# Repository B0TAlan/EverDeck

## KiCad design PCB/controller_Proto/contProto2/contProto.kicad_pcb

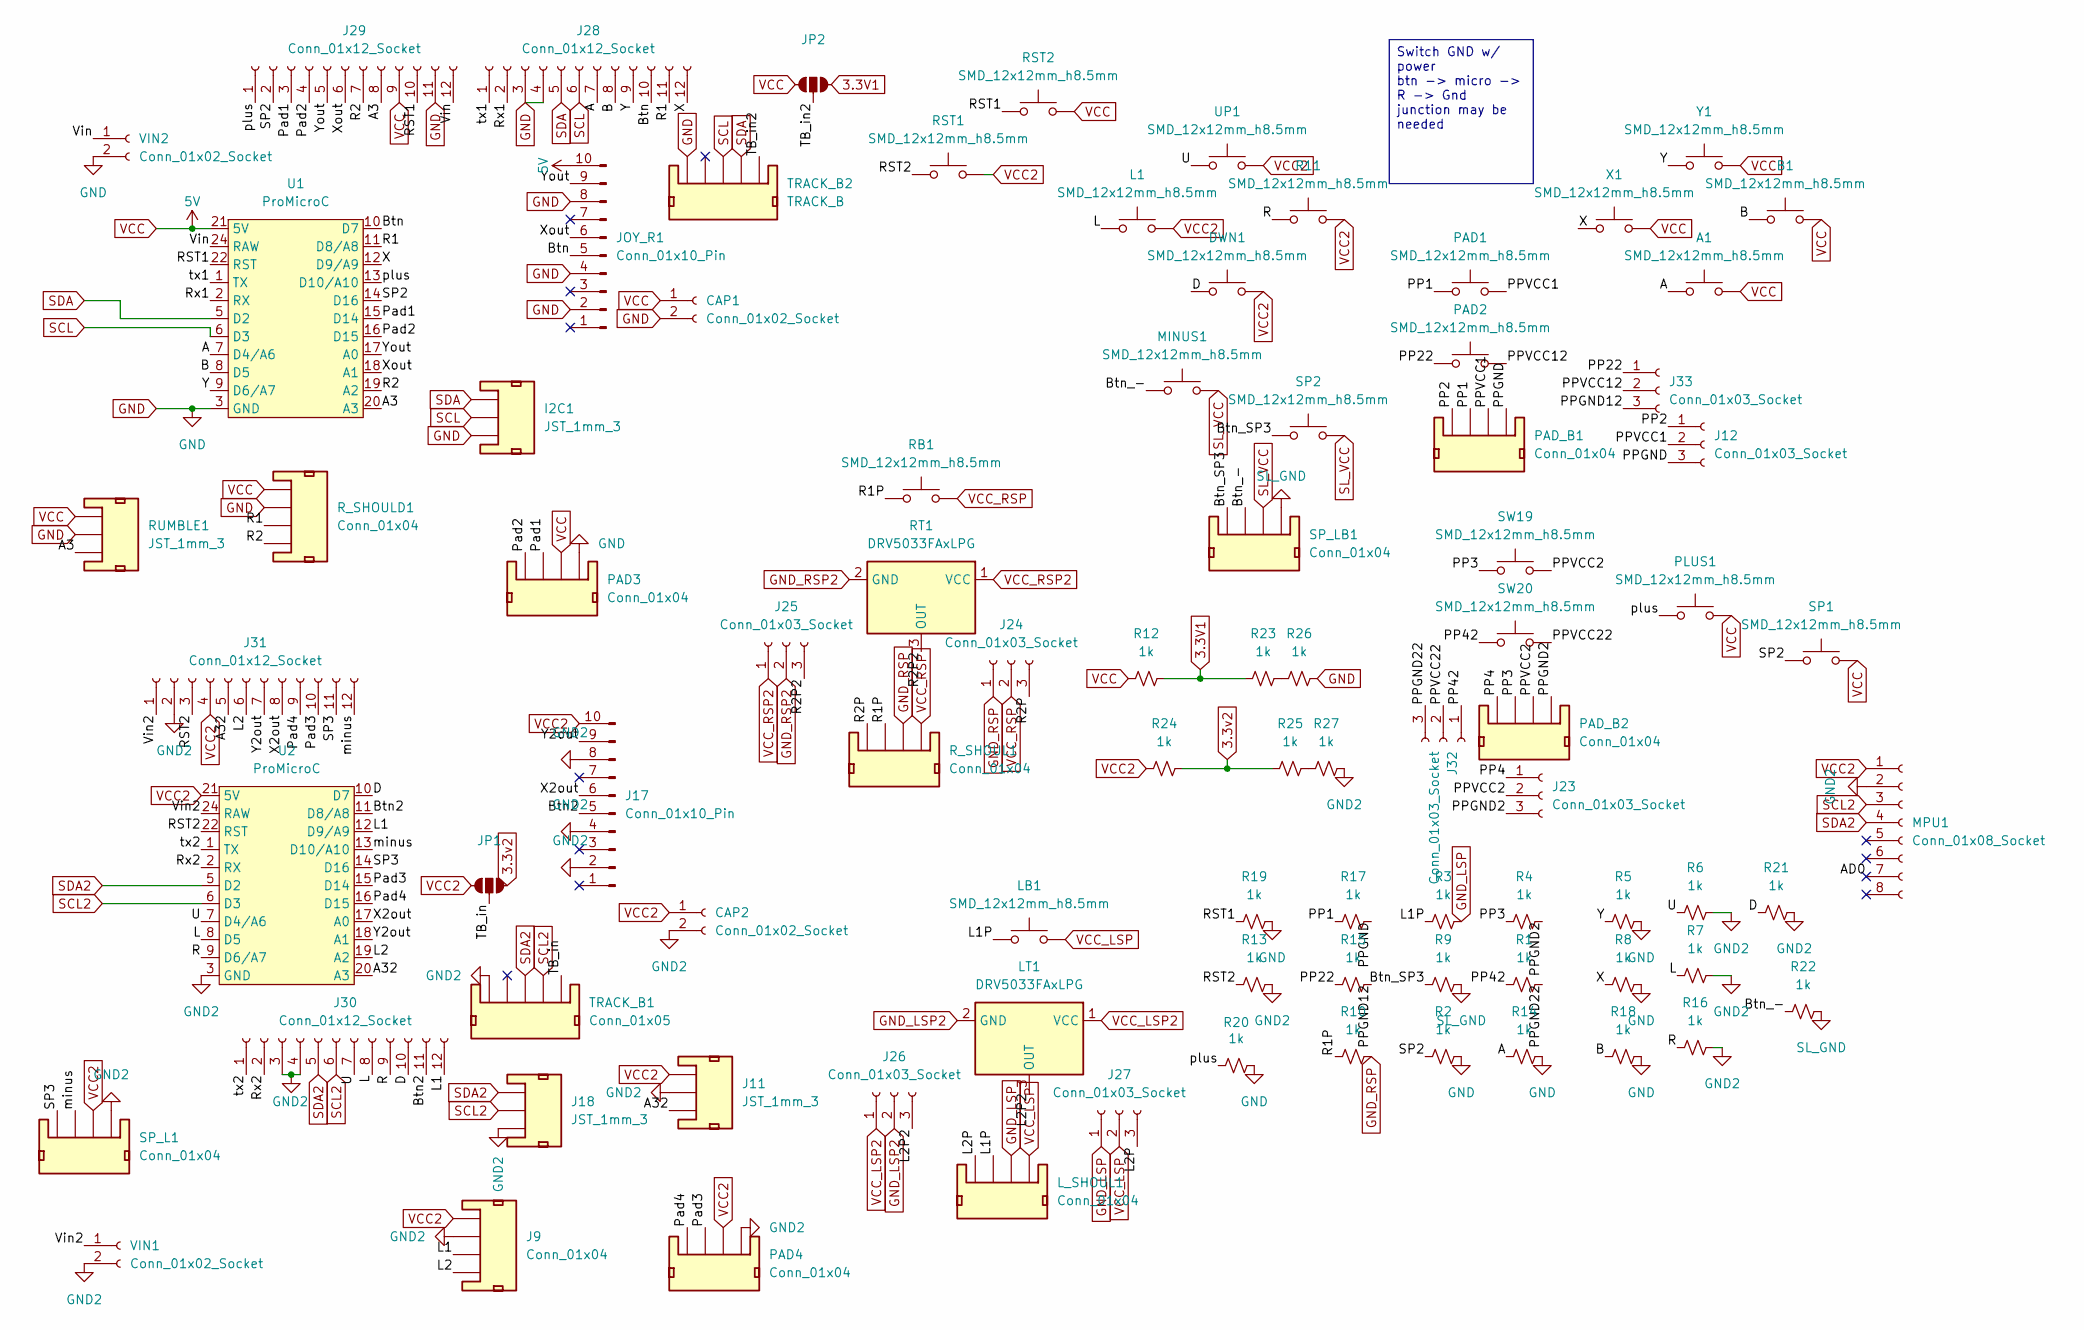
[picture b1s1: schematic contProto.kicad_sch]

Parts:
A1: SMD_12x12mm_h8.5mm; SW_Tactile_SPST_NO_Straight_CK_PTS636Sx25SMTRLFS; Mfg Part# EG4904TR-ND
B1: SMD_12x12mm_h8.5mm; SW_Tactile_SPST_NO_Straight_CK_PTS636Sx25SMTRLFS; Mfg Part# EG4904TR-ND
CAP1, CAP2: Conn_01x02_Socket; PinSocket_1x02_P2.54mm_Vertical
DWN1: SMD_12x12mm_h8.5mm; SW_Tactile_SPST_NO_Straight_CK_PTS636Sx25SMTRLFS; Mfg Part# EG4904TR-ND
I2C1: JST_1mm_3; JST_GH_BM03B-GHS-TBT_1x03-1MP_P1.25mm_Vertical
J9: Conn_01x04; Amphenol_F32Q-1A7x1-11004_1x04-1MP_P0.5mm_Horizontal
J11: JST_1mm_3; PinHeader_1x03_P2.54mm_Vertical
J12, J23, J24, J25, J26, J27, J32, J33: Conn_01x03_Socket; PinSocket_1x03_P2.54mm_Vertical
J17: Conn_01x10_Pin; Amphenol_F32Q-1A7x1-11010_1x10-1MP_P0.5mm_Horizontal
J18: JST_1mm_3; JST_GH_BM03B-GHS-TBT_1x03-1MP_P1.25mm_Vertical
J28, J29, J30, J31: Conn_01x12_Socket; PinSocket_1x12_P2.54mm_Vertical
JOY_R1: Conn_01x10_Pin; Amphenol_F32Q-1A7x1-11010_1x10-1MP_P0.5mm_Horizontal
JP1, JP2: Jumper_3_NO
L1: SMD_12x12mm_h8.5mm; SW_Tactile_SPST_NO_Straight_CK_PTS636Sx25SMTRLFS; Mfg Part# EG4904TR-ND
LB1: SMD_12x12mm_h8.5mm; SW_Tactile_SPST_NO_Straight_CK_PTS636Sx25SMTRLFS; Mfg Part# EG4904TR-ND
LT1: DRV5033FAxLPG; TO-92_Inline
L_SHOUL1: Conn_01x04; Amphenol_F32Q-1A7x1-11004_1x04-1MP_P0.5mm_Horizontal
MINUS1: SMD_12x12mm_h8.5mm; SW_Tactile_SPST_NO_Straight_CK_PTS636Sx25SMTRLFS; Mfg Part# EG4904TR-ND
MPU1: Conn_01x08_Socket; PinSocket_1x08_P2.54mm_Vertical
PAD1, PAD2: SMD_12x12mm_h8.5mm; SW_Tactile_SPST_NO_Straight_CK_PTS636Sx25SMTRLFS; Mfg Part# EG4904TR-ND
PAD3, PAD4: Conn_01x04; Amphenol_F32Q-1A7x1-11004_1x04-1MP_P0.5mm_Horizontal
PAD_B1, PAD_B2: Conn_01x04; Amphenol_F32Q-1A7x1-11004_1x04-1MP_P0.5mm_Horizontal
PLUS1: SMD_12x12mm_h8.5mm; SW_Tactile_SPST_NO_Straight_CK_PTS636Sx25SMTRLFS; Mfg Part# EG4904TR-ND
R1, R2, R3, R4, R5, R6, R7, R8, R9, R10, R12, R13, R14, R15, R16, R17, R18, R19, R20, R21, R22, R23, R24, R25, R26, R27: 1k; R_0805_2012Metric
R11: SMD_12x12mm_h8.5mm; SW_Tactile_SPST_NO_Straight_CK_PTS636Sx25SMTRLFS; Mfg Part# EG4904TR-ND
RB1: SMD_12x12mm_h8.5mm; SW_Tactile_SPST_NO_Straight_CK_PTS636Sx25SMTRLFS; Mfg Part# EG4904TR-ND
RST1, RST2: SMD_12x12mm_h8.5mm; SW_Tactile_SPST_NO_Straight_CK_PTS636Sx25SMTRLFS; Mfg Part# EG4904TR-ND
RT1: DRV5033FAxLPG; TO-92_Inline
RUMBLE1: JST_1mm_3; PinHeader_1x03_P2.54mm_Vertical
R_SHOUL1: Conn_01x04; Amphenol_F32Q-1A7x1-11004_1x04-1MP_P0.5mm_Horizontal
R_SHOULD1: Conn_01x04; Amphenol_F32Q-1A7x1-11004_1x04-1MP_P0.5mm_Horizontal
SP1, SP2: SMD_12x12mm_h8.5mm; SW_Tactile_SPST_NO_Straight_CK_PTS636Sx25SMTRLFS; Mfg Part# EG4904TR-ND
SP_L1: Conn_01x04; Amphenol_F32Q-1A7x1-11004_1x04-1MP_P0.5mm_Horizontal
SP_LB1: Conn_01x04; Amphenol_F32Q-1A7x1-11004_1x04-1MP_P0.5mm_Horizontal
SW19, SW20: SMD_12x12mm_h8.5mm; SW_Tactile_SPST_NO_Straight_CK_PTS636Sx25SMTRLFS; Mfg Part# EG4904TR-ND
TRACK_B1: Conn_01x05; PinHeader_1x05_P2.54mm_Vertical
TRACK_B2: TRACK_B; PinHeader_1x05_P2.54mm_Vertical
U1, U2: ProMicroC
UP1: SMD_12x12mm_h8.5mm; SW_Tactile_SPST_NO_Straight_CK_PTS636Sx25SMTRLFS; Mfg Part# EG4904TR-ND
VIN1, VIN2: Conn_01x02_Socket; PinSocket_1x02_P2.54mm_Vertical
X1: SMD_12x12mm_h8.5mm; SW_Tactile_SPST_NO_Straight_CK_PTS636Sx25SMTRLFS; Mfg Part# EG4904TR-ND
Y1: SMD_12x12mm_h8.5mm; SW_Tactile_SPST_NO_Straight_CK_PTS636Sx25SMTRLFS; Mfg Part# EG4904TR-ND

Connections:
3.3V1: JP2.3 (C), R12.2, R23.1
3.3v2: JP1.3 (C), R24.2, R25.1
/A: A1.1, J28.7, R14.1, U1.7 (D4/A6)
/A3: J29.8, RUMBLE1.3, U1.20 (A3)
/A32: J11.3, J31.5, U2.20 (A3)
/AD0: MPU1.7
/B: B1.1, J28.8, R18.1, U1.8 (D5)
/Btn: J28.10, JOY_R1.5, U1.10 (D7)
/Btn2: J17.5, J30.11, U2.11 (D8/A8)
/Btn_-: MINUS1.1, R22.1, SP_LB1.3
/Btn_SP3: R9.1, SP2.1, SP_LB1.4
/D: DWN1.1, J30.10, R21.1, U2.10 (D7)
/L: J30.8, L1.1, R7.1, U2.8 (D5)
/L1: J9.3, J30.12, U2.12 (D9/A9)
/L1P: LB1.1, L_SHOUL1.3, R3.1
/L2: J9.4, J31.6, U2.19 (A2)
/L2P: J27.3, L_SHOUL1.4
/L2P2: J26.3, LT1.3 (OUT)
/PP1: PAD1.1, PAD_B1.3, R17.1
/PP2: J12.1, PAD_B1.4
/PP3: PAD_B2.3, R4.1, SW19.1
/PP4: J23.1, PAD_B2.4
/PP22: J33.1, PAD2.1, R15.1
/PP42: J32.1, R1.1, SW20.1
/PPGND: J12.3, PAD_B1.1, R17.2
/PPGND2: J23.3, PAD_B2.1, R4.2
/PPGND12: J33.3, R15.2
/PPGND22: J32.3, R1.2
/PPVCC1: J12.2, PAD1.2, PAD_B1.2
/PPVCC2: J23.2, PAD_B2.2, SW19.2
/PPVCC12: J33.2, PAD2.2
/PPVCC22: J32.2, SW20.2
/Pad1: J29.3, PAD3.3, U1.15 (D14)
/Pad2: J29.4, PAD3.4, U1.16 (D15)
/Pad3: J31.10, PAD4.3, U2.15 (D14)
/Pad4: J31.9, PAD4.4, U2.16 (D15)
/R: J30.9, R11.1, R16.1, U2.9 (D6/A7)
/R1: J28.11, R_SHOULD1.3, U1.11 (D8/A8)
/R1P: R10.1, RB1.1, R_SHOUL1.3
/R2: J29.7, R_SHOULD1.4, U1.19 (A2)
/R2P: J24.3, R_SHOUL1.4
/R2P2: J25.3, RT1.3 (OUT)
/RST1: J29.10, R19.1, RST2.1, U1.22 (RST)
/RST2: J31.3, R13.1, RST1.1, U2.22 (RST)
/Rx1: J28.2, U1.2 (RX)
/Rx2: J30.2, U2.2 (RX)
/SP2: J29.2, R2.1, SP1.1, U1.14 (D16)
/SP3: J31.11, SP_L1.4, U2.14 (D16)
/TB_in: JP1.2 (B), TRACK_B1.1
/TB_in2: JP2.2 (B), TRACK_B2.1
/U: J30.7, R6.1, U2.7 (D4/A6), UP1.1
/Vin: J29.12, U1.24 (RAW), VIN2.1
/Vin2: J31.1, U2.24 (RAW), VIN1.1
/X: J28.12, R8.1, U1.12 (D9/A9), X1.1
/X2out: J17.6, J31.8, U2.17 (A0)
/Xout: J29.6, JOY_R1.6, U1.18 (A1)
/Y: J28.9, R5.1, U1.9 (D6/A7), Y1.1
/Y2out: J17.9, J31.7, U2.18 (A1)
/Yout: J29.5, JOY_R1.9, U1.17 (A0)
/minus: J31.12, SP_L1.3, U2.13 (D10/A10)
/plus: J29.1, PLUS1.1, R20.1, U1.13 (D10/A10)
/tx1: J28.1, U1.1 (TX)
/tx2: J30.1, U2.1 (TX)
GND: CAP1.2, I2C1.3, J28.3, J28.4, J29.11, JOY_R1.2, JOY_R1.4, JOY_R1.8, PAD3.1, R2.2, R5.2, R8.2, R14.2, R18.2, R19.2, R20.2, R26.2, RUMBLE1.2, R_SHOULD1.2, TRACK_B2.5, U1.3 (GND), U1.4 (GND), U1.23 (GND), VIN2.2
GND2: CAP2.2, J9.2, J11.2, J17.2, J17.4, J17.8, J18.3, J30.3, J30.4, J31.2, MPU1.2, PAD4.1, R6.2, R7.2, R13.2, R16.2, R21.2, R27.2, SP_L1.1, TRACK_B1.5, U2.3 (GND), U2.4 (GND), U2.23 (GND), VIN1.2
GND_LSP: J27.1, L_SHOUL1.2, R3.2
GND_LSP2: J26.2, LT1.2 (GND)
GND_RSP: J24.1, R10.2, R_SHOUL1.2
GND_RSP2: J25.2, RT1.2 (GND)
unnamed: R23.2, R26.1
unnamed: R25.2, R27.1
SCL: I2C1.2, J28.6, TRACK_B2.3, U1.6 (D3)
SCL2: J18.2, J30.6, MPU1.3, TRACK_B1.2, U2.6 (D3)
SDA: I2C1.1, J28.5, TRACK_B2.2, U1.5 (D2)
SDA2: J18.1, J30.5, MPU1.4, TRACK_B1.3, U2.5 (D2)
SL_GND: R9.2, R22.2, SP_LB1.1
SL_VCC: MINUS1.2, SP2.2, SP_LB1.2
VCC: A1.2, B1.2, CAP1.1, J29.9, JOY_R1.10, JP2.1 (A), PAD3.2, PLUS1.2, R12.1, RST2.2, RUMBLE1.1, R_SHOULD1.1, SP1.2, U1.21 (5V), X1.2, Y1.2
VCC2: CAP2.1, DWN1.2, J9.1, J11.1, J17.10, J31.4, JP1.1 (A), L1.2, MPU1.1, PAD4.2, R11.2, R24.1, RST1.2, SP_L1.2, U2.21 (5V), UP1.2
VCC_LSP: J27.2, LB1.2, L_SHOUL1.1
VCC_LSP2: J26.1, LT1.1 (VCC)
VCC_RSP: J24.2, RB1.2, R_SHOUL1.1
VCC_RSP2: J25.1, RT1.1 (VCC)

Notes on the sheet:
Switch GND w/ power btn -> micro -> R -> Gnd junction may be needed

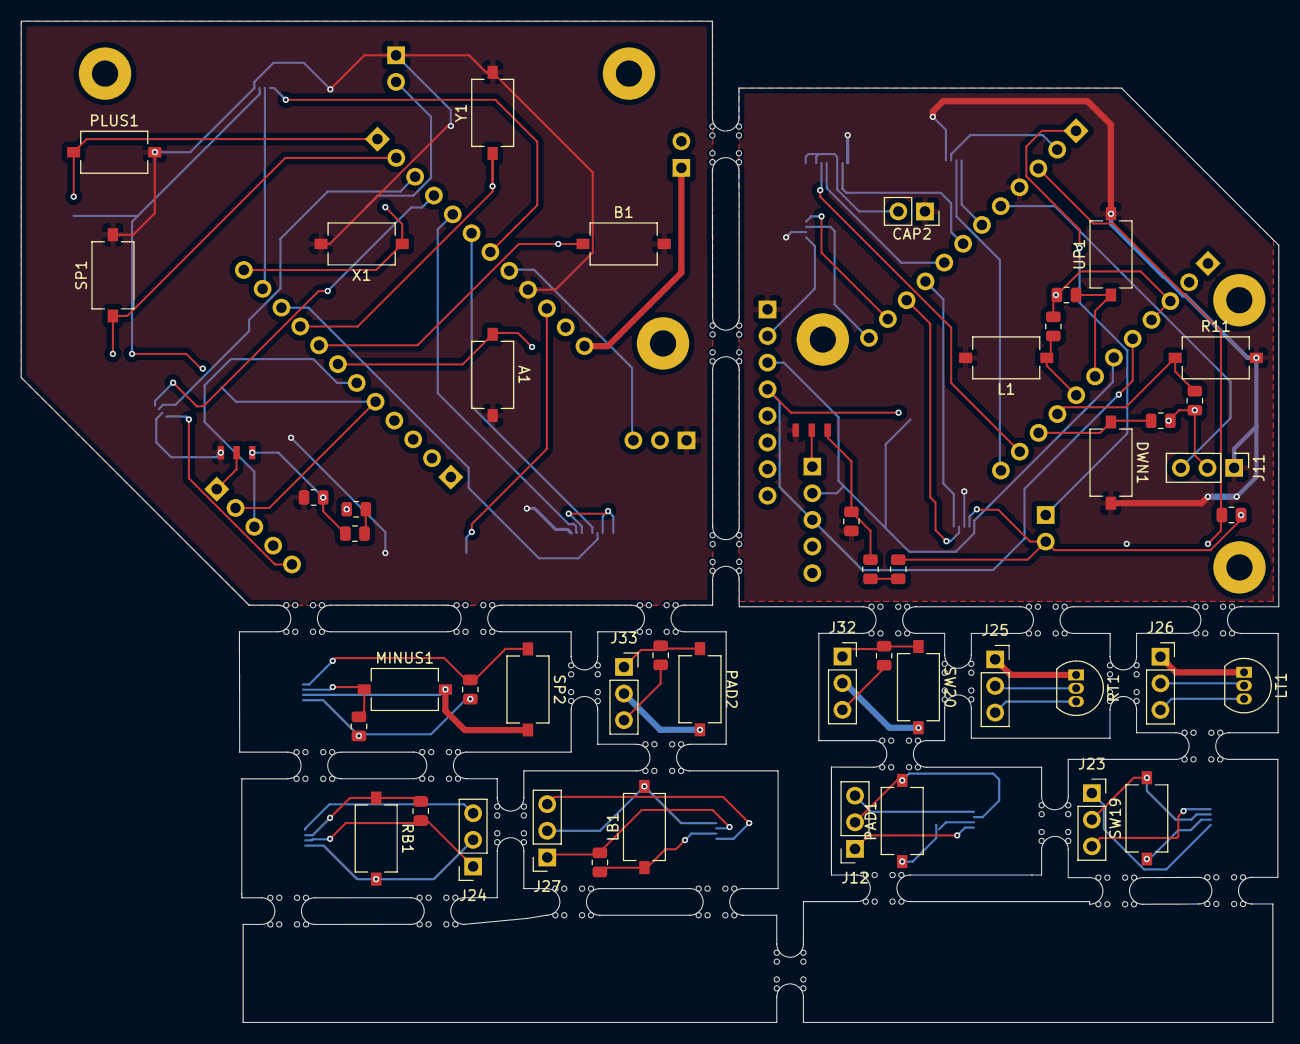
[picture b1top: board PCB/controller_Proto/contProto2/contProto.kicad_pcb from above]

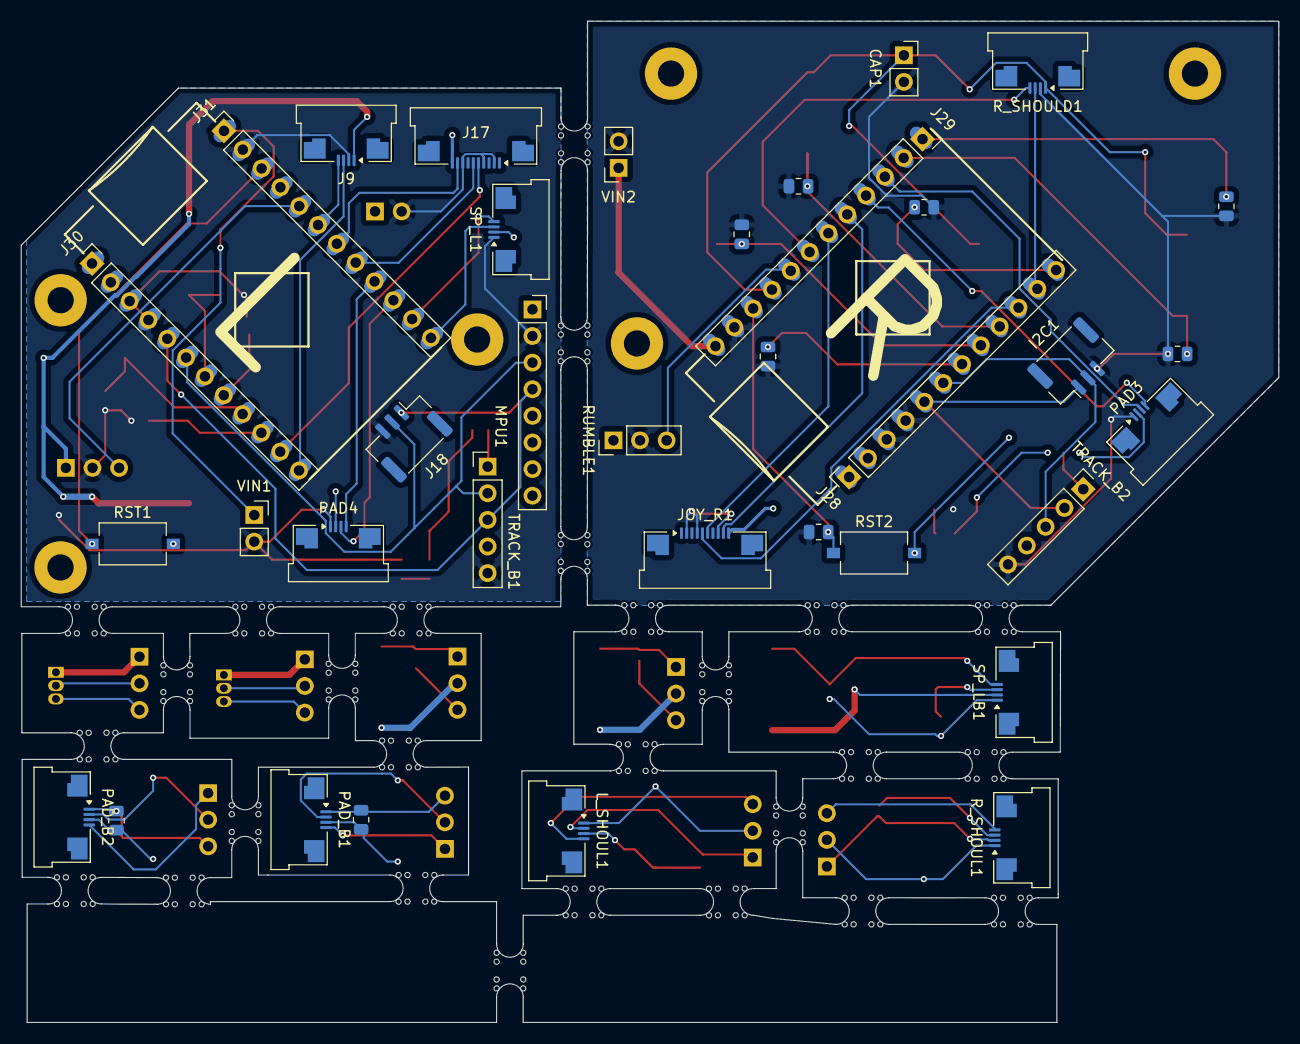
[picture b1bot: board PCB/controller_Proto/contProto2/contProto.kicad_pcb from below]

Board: 2 copper layers, 120.0 x 95.5 mm, 87 parts (38 on the bottom side), 82 nets.

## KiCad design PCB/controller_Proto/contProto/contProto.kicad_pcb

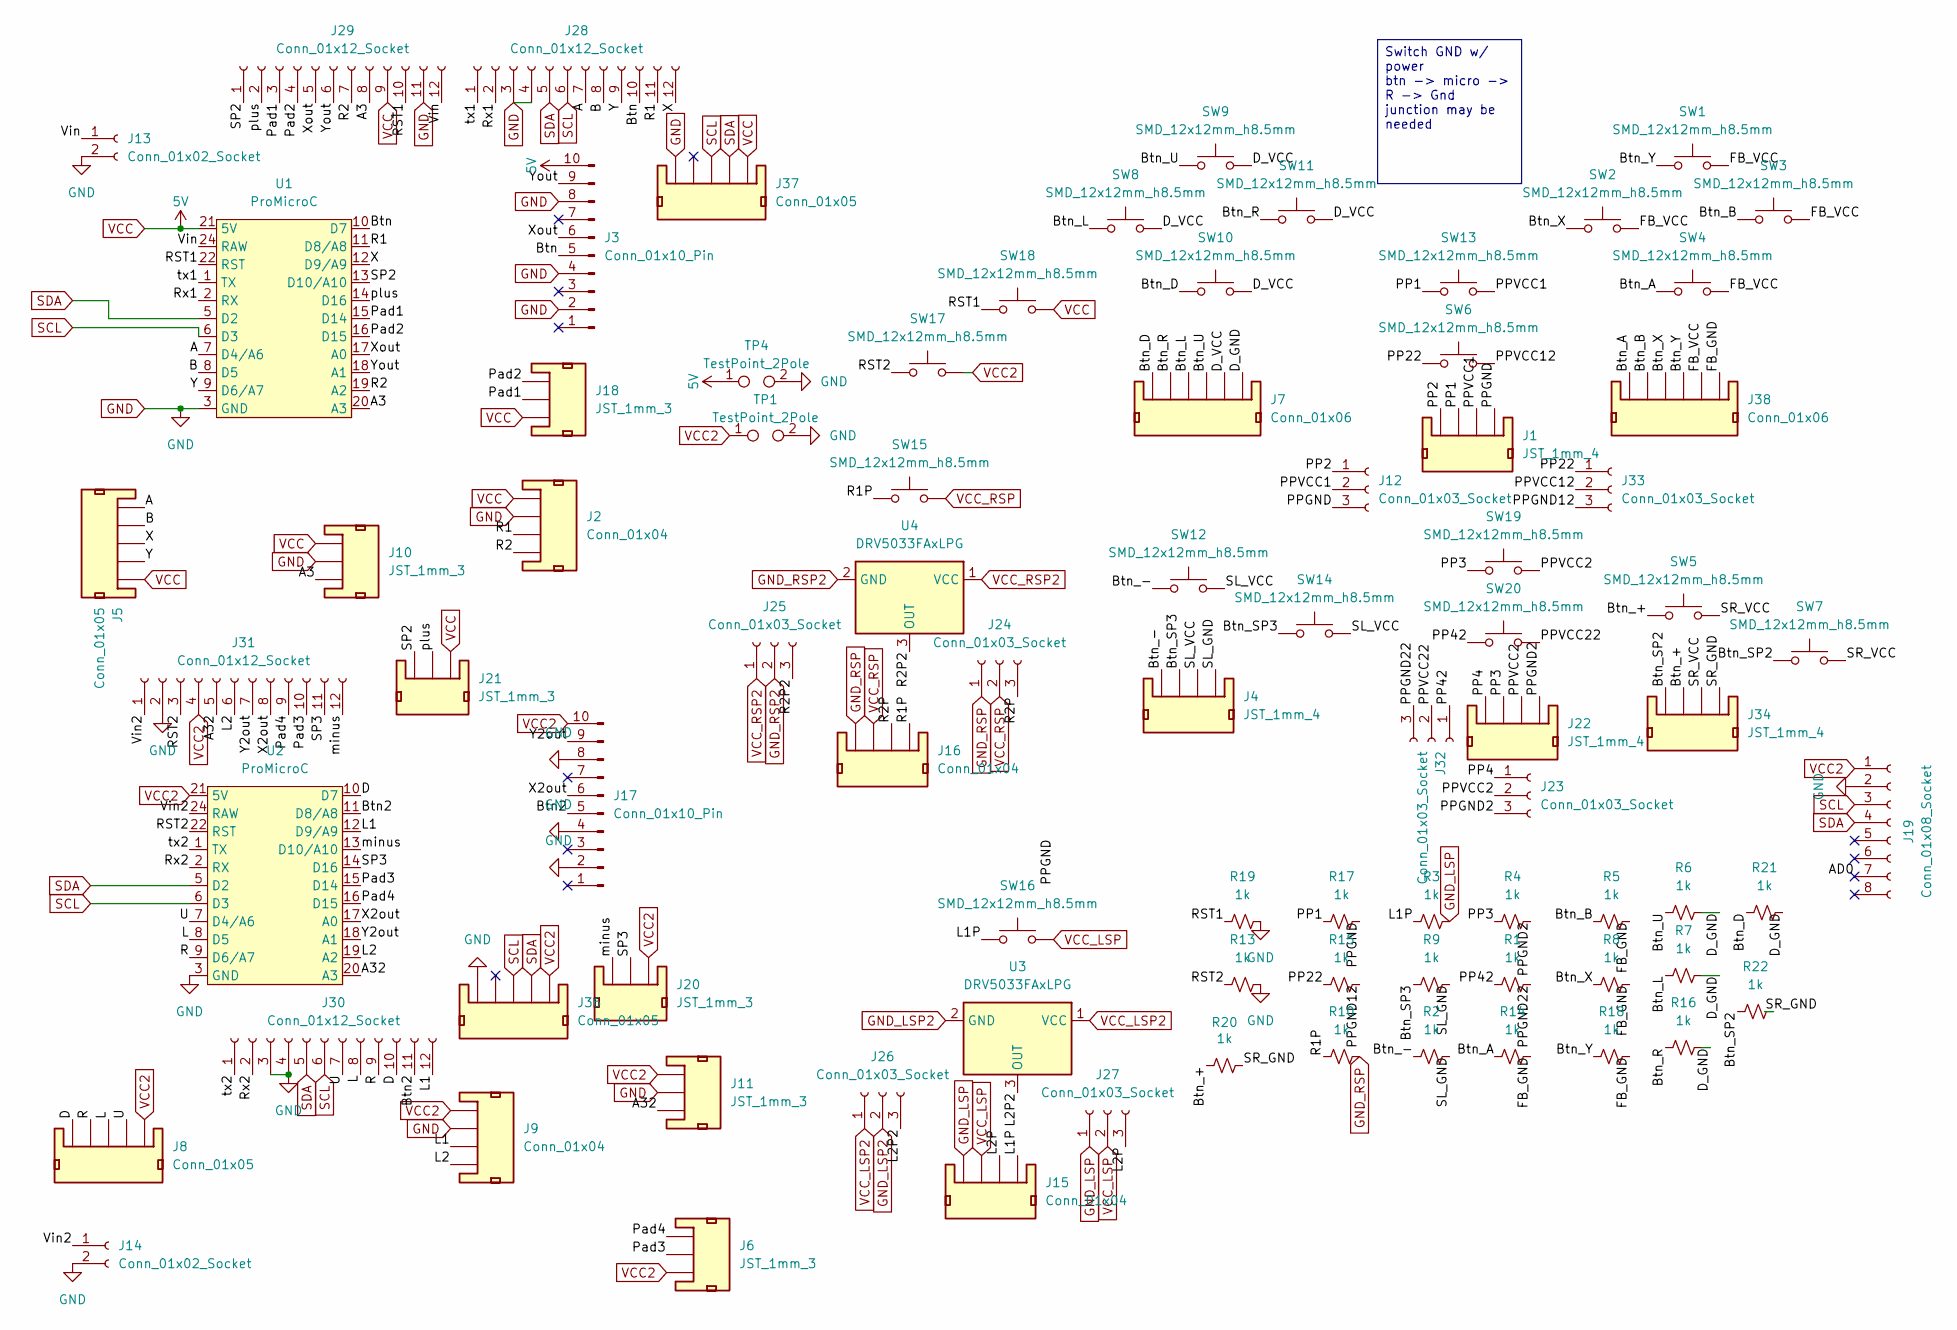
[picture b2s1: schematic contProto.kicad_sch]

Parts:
J1, J4, J22, J34: JST_1mm_4; JST_1x04_P1.0mm_Horizontal_SMD
J2, J9, J15, J16: Conn_01x04; JST_GH_BM04B-GHS-TBT_1x04-1MP_P1.25mm_Vertical
J3, J17: Conn_01x10_Pin; Amphenol_F32Q-1A7x1-11010_1x10-1MP_P0.5mm_Horizontal
J5, J8, J36, J37: Conn_01x05; JST_GH_BM05B-GHS-TBT_1x05-1MP_P1.25mm_Vertical
J6, J10, J11, J18, J20, J21: JST_1mm_3; JST_GH_BM03B-GHS-TBT_1x03-1MP_P1.25mm_Vertical
J7, J38: Conn_01x06; JST_1x06_P1.0mm_Horizontal_SMD
J12, J23, J24, J25, J26, J27, J32, J33: Conn_01x03_Socket; PinSocket_1x03_P2.54mm_Vertical
J13, J14: Conn_01x02_Socket; PinSocket_1x02_P2.54mm_Vertical
J19: Conn_01x08_Socket; PinSocket_1x08_P2.54mm_Vertical
J28, J29, J30, J31: Conn_01x12_Socket; PinSocket_1x12_P2.54mm_Vertical
R1, R2, R3, R4, R5, R6, R7, R8, R9, R10, R13, R14, R15, R16, R17, R18, R19, R20, R21, R22: 1k; R_0402_1005Metric
SW1, SW2, SW3, SW4, SW5, SW6, SW7, SW8, SW9, SW10, SW11, SW12, SW13, SW14, SW15, SW16, SW17, SW18, SW19, SW20: SMD_12x12mm_h8.5mm; SW_Tactile_SPST_NO_Straight_CK_PTS636Sx25SMTRLFS; Mfg Part# EG4904TR-ND
TP1, TP4: TestPoint_2Pole; TestPoint_Bridge_Pitch2.0mm_Drill0.7mm
U1, U2: ProMicroC
U3, U4: DRV5033FAxLPG; TO-92_Inline

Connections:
/A: J5.5, J28.7, U1.7 (D4/A6)
/A3: J10.3, J29.8, U1.20 (A3)
/A32: J11.3, J31.5, U2.20 (A3)
/AD0: J19.7
/B: J5.4, J28.8, U1.8 (D5)
/Btn: J3.5, J28.10, U1.10 (D7)
/Btn2: J17.5, J30.11, U2.11 (D8/A8)
/Btn_+: J34.3, R20.1, SW5.1
/Btn_-: J4.4, R2.1, SW12.1
/Btn_A: J38.6, R14.1, SW4.1
/Btn_B: J38.5, R5.1, SW3.1
/Btn_D: J7.6, R21.1, SW10.1
/Btn_L: J7.4, R7.1, SW8.1
/Btn_R: J7.5, R16.1, SW11.1
/Btn_SP2: J34.4, R22.1, SW7.1
/Btn_SP3: J4.3, R9.1, SW14.1
/Btn_U: J7.3, R6.1, SW9.1
/Btn_X: J38.4, R8.1, SW2.1
/Btn_Y: J38.3, R18.1, SW1.1
/D: J8.5, J30.10, U2.10 (D7)
/D_GND: J7.1, R6.2, R7.2, R16.2, R21.2
/D_VCC: J7.2, SW8.2, SW9.2, SW10.2, SW11.2
/FB_GND: J38.1, R5.2, R8.2, R14.2, R18.2
/FB_VCC: J38.2, SW1.2, SW2.2, SW3.2, SW4.2
/L: J8.3, J30.8, U2.8 (D5)
/L1: J9.3, J30.12, U2.12 (D9/A9)
/L1P: J15.1, R3.1, SW16.1
/L2: J9.4, J31.6, U2.19 (A2)
/L2P: J15.2, J27.3
/L2P2: J26.3, U3.3 (OUT)
/PP1: J1.3, R17.1, SW13.1
/PP2: J1.4, J12.1
/PP3: J22.3, R4.1, SW19.1
/PP4: J22.4, J23.1
/PP22: J33.1, R15.1, SW6.1
/PP42: J32.1, R1.1, SW20.1
/PPGND: J1.1, J12.3, R17.2
/PPGND2: J22.1, J23.3, R4.2
/PPGND12: J33.3, R15.2
/PPGND22: J32.3, R1.2
/PPVCC1: J1.2, J12.2, SW13.2
/PPVCC2: J22.2, J23.2, SW19.2
/PPVCC12: J33.2, SW6.2
/PPVCC22: J32.2, SW20.2
/Pad1: J18.2, J29.3, U1.15 (D14)
/Pad2: J18.1, J29.4, U1.16 (D15)
/Pad3: J6.2, J31.10, U2.15 (D14)
/Pad4: J6.1, J31.9, U2.16 (D15)
/R: J8.4, J30.9, U2.9 (D6/A7)
/R1: J2.3, J28.11, U1.11 (D8/A8)
/R1P: J16.1, R10.1, SW15.1
/R2: J2.4, J29.7, U1.19 (A2)
/R2P: J16.2, J24.3
/R2P2: J25.3, U4.3 (OUT)
/RST1: J29.10, R19.1, SW18.1, U1.22 (RST)
/RST2: J31.3, R13.1, SW17.1, U2.22 (RST)
/Rx1: J28.2, U1.2 (RX)
/Rx2: J30.2, U2.2 (RX)
/SL_GND: J4.1, R2.2, R9.2
/SL_VCC: J4.2, SW12.2, SW14.2
/SP2: J21.3, J29.1, U1.13 (D10/A10)
/SP3: J20.2, J31.11, U2.14 (D16)
/SR_GND: J34.1, R20.2, R22.2
/SR_VCC: J34.2, SW5.2, SW7.2
/U: J8.2, J30.7, U2.7 (D4/A6)
/Vin: J13.1, J29.12, U1.24 (RAW)
/Vin2: J14.1, J31.1, U2.24 (RAW)
/X: J5.3, J28.12, U1.12 (D9/A9)
/X2out: J17.6, J31.8, U2.17 (A0)
/Xout: J3.6, J29.5, U1.17 (A0)
/Y: J5.2, J28.9, U1.9 (D6/A7)
/Y2out: J17.9, J31.7, U2.18 (A1)
/Yout: J3.9, J29.6, U1.18 (A1)
/minus: J20.3, J31.12, U2.13 (D10/A10)
/plus: J21.2, J29.2, U1.14 (D16)
/tx1: J28.1, U1.1 (TX)
/tx2: J30.1, U2.1 (TX)
GND: J2.2, J3.2, J3.4, J3.8, J9.2, J10.2, J11.2, J13.2, J14.2, J17.2, J17.4, J17.8, J19.2, J28.3, J28.4, J29.11, J30.3, J30.4, J31.2, J36.5, J37.5, R13.2, R19.2, TP1.2, TP4.2, U1.3 (GND), U1.4 (GND), U1.23 (GND), U2.3 (GND), U2.4 (GND), U2.23 (GND)
GND_LSP: J15.4, J27.1, R3.2
GND_LSP2: J26.2, U3.2 (GND)
GND_RSP: J16.4, J24.1, R10.2
GND_RSP2: J25.2, U4.2 (GND)
SCL: J19.3, J28.6, J30.6, J36.3, J37.3, U1.6 (D3), U2.6 (D3)
SDA: J19.4, J28.5, J30.5, J36.2, J37.2, U1.5 (D2), U2.5 (D2)
VCC: J2.1, J3.10, J5.1, J10.1, J18.3, J21.1, J29.9, J37.1, SW18.2, TP4.1, U1.21 (5V)
VCC2: J6.3, J8.1, J9.1, J11.1, J17.10, J19.1, J20.1, J31.4, J36.1, SW17.2, TP1.1, U2.21 (5V)
VCC_LSP: J15.3, J27.2, SW16.2
VCC_LSP2: J26.1, U3.1 (VCC)
VCC_RSP: J16.3, J24.2, SW15.2
VCC_RSP2: J25.1, U4.1 (VCC)

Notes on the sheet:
Switch GND w/ power btn -> micro -> R -> Gnd junction may be needed

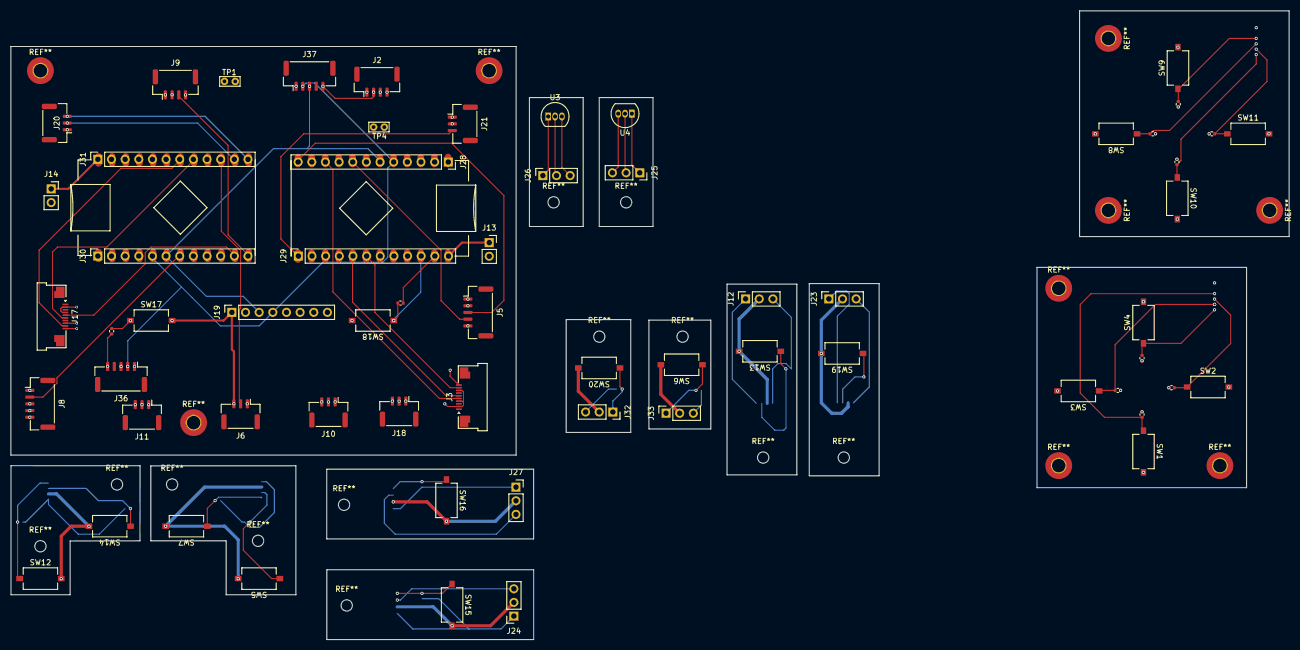
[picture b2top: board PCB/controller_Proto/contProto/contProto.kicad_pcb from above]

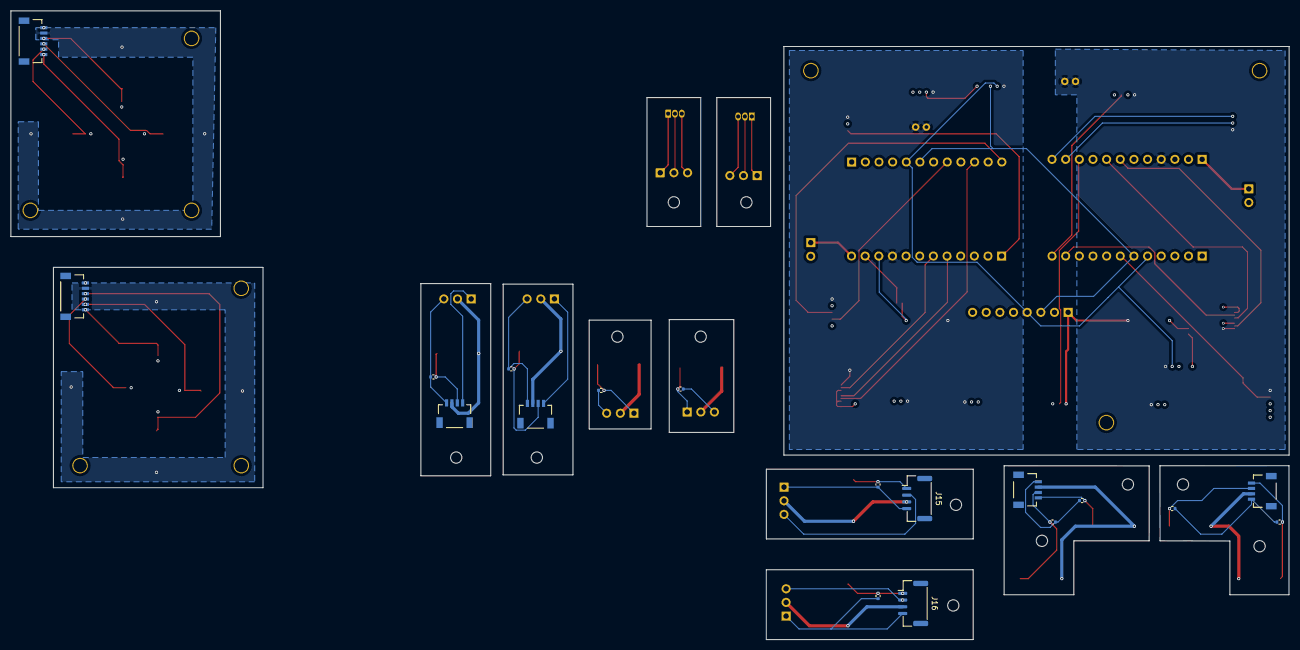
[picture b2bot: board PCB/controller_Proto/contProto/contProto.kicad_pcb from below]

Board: 4 copper layers, 237.9 x 117.0 mm, 83 parts (18 on the bottom side), 89 nets.

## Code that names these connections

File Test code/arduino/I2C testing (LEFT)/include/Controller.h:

#ifndef CONTROLLER_H
#define CONTROLLER_H
#include<Arduino.h>
#include<Sinput.h>


//uint8_t button_pins[] = {7, 8, 9, 10, 11, 12, 13, 14, 15, 16};

namespace ControllerButtons {// this struct contains a bitmap for each button to avoid adding padding bits
    static constexpr uint8_t A           = 0; //Btn0
    static constexpr uint8_t B           = 1; //Btn1
    static constexpr uint8_t X           = 4; //Btn2
    static constexpr uint8_t Y           = 3; //Btn3
    static constexpr uint8_t LB          = 6; //Btn4
    static constexpr uint8_t RB          = 7; //Btn5
    static constexpr uint8_t BACK        = 10; //Btn6
    static constexpr uint8_t START       = 11; //Btn7
    static constexpr uint8_t L3          = 13; //Btn8
    static constexpr uint8_t R3          = 14; //Btn9
    static constexpr uint8_t MENU        = 12; //Btn10
    static constexpr uint8_t L_TRACK_CLK = 13; //Btn11
    static constexpr uint8_t R_TRACK_CLK = 14; //Btn12
    static constexpr uint8_t UP          = 15; //Btn13
    static constexpr uint8_t DWN         = 16; //Btn14
    static constexpr uint8_t LEFT        = 17; //Btn15
    static constexpr uint8_t RIGHT       = 18; //Btn16
    static constexpr uint8_t PAD1        = 19; //Btn17
    static constexpr uint8_t PAD2        = 20; //Btn18
    static constexpr uint8_t PAD3        = 21; //Btn19
    

    static constexpr uint8_t Masks[] = {A, B, X, Y, LB, RB, BACK, START, L3, R3, MENU, L_TRACK_CLK, R_TRACK_CLK, UP, DWN, LEFT, RIGHT, PAD1, PAD2, PAD3 };
};
//int xOut;
//int yOut;
//int r2;
//int l2;

class Controller{
    public:
    Controller(uint8_t* pins, size_t pinNum, uint16_t* ls, uint16_t* rs, uint16_t* trig);
    Controller(uint8_t* pins, size_t pinNum, uint16_t* ls, uint16_t* rs, uint16_t* trig, int* dz);
    
    void setBut(uint8_t Button, int value);

    void bindBut(uint8_t Button, int pin);

    void send();

    void begin();

    void stop();

    void start();

    void printButtonDebug();
    
    uint8_t deb(uint8_t pin);

    private:
    //vars
    int *deadZone; // {ls,rs,lt,rt}
    bool STATE = true;
    uint16_t *lStick, *rStick, *triggers; // analog stick {x, y} & triggers {L, R}
    uint8_t *buttons, *Dpad; 
    Gamepad_Input_Report_t  input  = {};  // zero-initialised on startup
    Gamepad_Output_Report_t output = {};
    size_t bn;

    //funcs
    uint8_t *readBut(uint8_t *pins);
    

    template <typename T>
static int get_index(const T* array, size_t size, T target) {
    for (size_t i = 0; i < size; i++) {
        if (array[i] == target) return (int)i;
    }
    return -1;
}

    

};

#endif

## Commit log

2025-12-27 Uploading Kicad project
2025-12-27 read me
2025-12-27 Read me update
2025-12-27 Fix formatting issues in README.md
2025-12-27 Change header from H1 to H2 in README.md
2025-12-28 adding more buttons
2026-01-04 adding code
2026-01-09 tinkering
    need resistors on all buttons
    ground needs to be separated still
2026-01-09 testing joystick w/ code
2026-01-09 pcb fixing
2026-01-10 fixing pcb
2026-01-12 PCB layout
2026-01-12 new code
2026-01-13 moooooorrrreeee cooooooddddeeee
2026-01-13 pcbeing
2026-01-13 ALL THE PLANES
2026-01-15 face but
2026-01-17 finnish shoulder borads
2026-01-19 failing with mouse bites
2026-01-19 no more errors and trackball ports
2026-01-19 I almost forgot the mounting holes
2026-01-20 testing the c++ waters
2026-01-23 move res big v
2026-01-26 Pcb redo
2026-01-27 MAJOR PCB REDESIGN
    shit here we go again
2026-01-28 final resesign and silk screen
2026-01-28 Big resistors
2026-02-18 final pcb
2026-03-02 adding mpu
2026-03-03 more
2026-03-10 from the debby
2026-04-03 Back to it
    use the slop machine (Claude) to test a usb descriptor
    debounce dosent work :(
2026-04-10 hid testing
2026-04-12 AHHHHHHHHHHH
    progress
2026-04-13 duiles
2026-04-26 skdjfa;lksd
    ajsdfkljas;dlkfjasldkfja;lksd
2026-06-04 touch up
2026-06-09 adding analog stuff
    i need to hook up a joystick :)
2026-06-09 MORE ANALOG
